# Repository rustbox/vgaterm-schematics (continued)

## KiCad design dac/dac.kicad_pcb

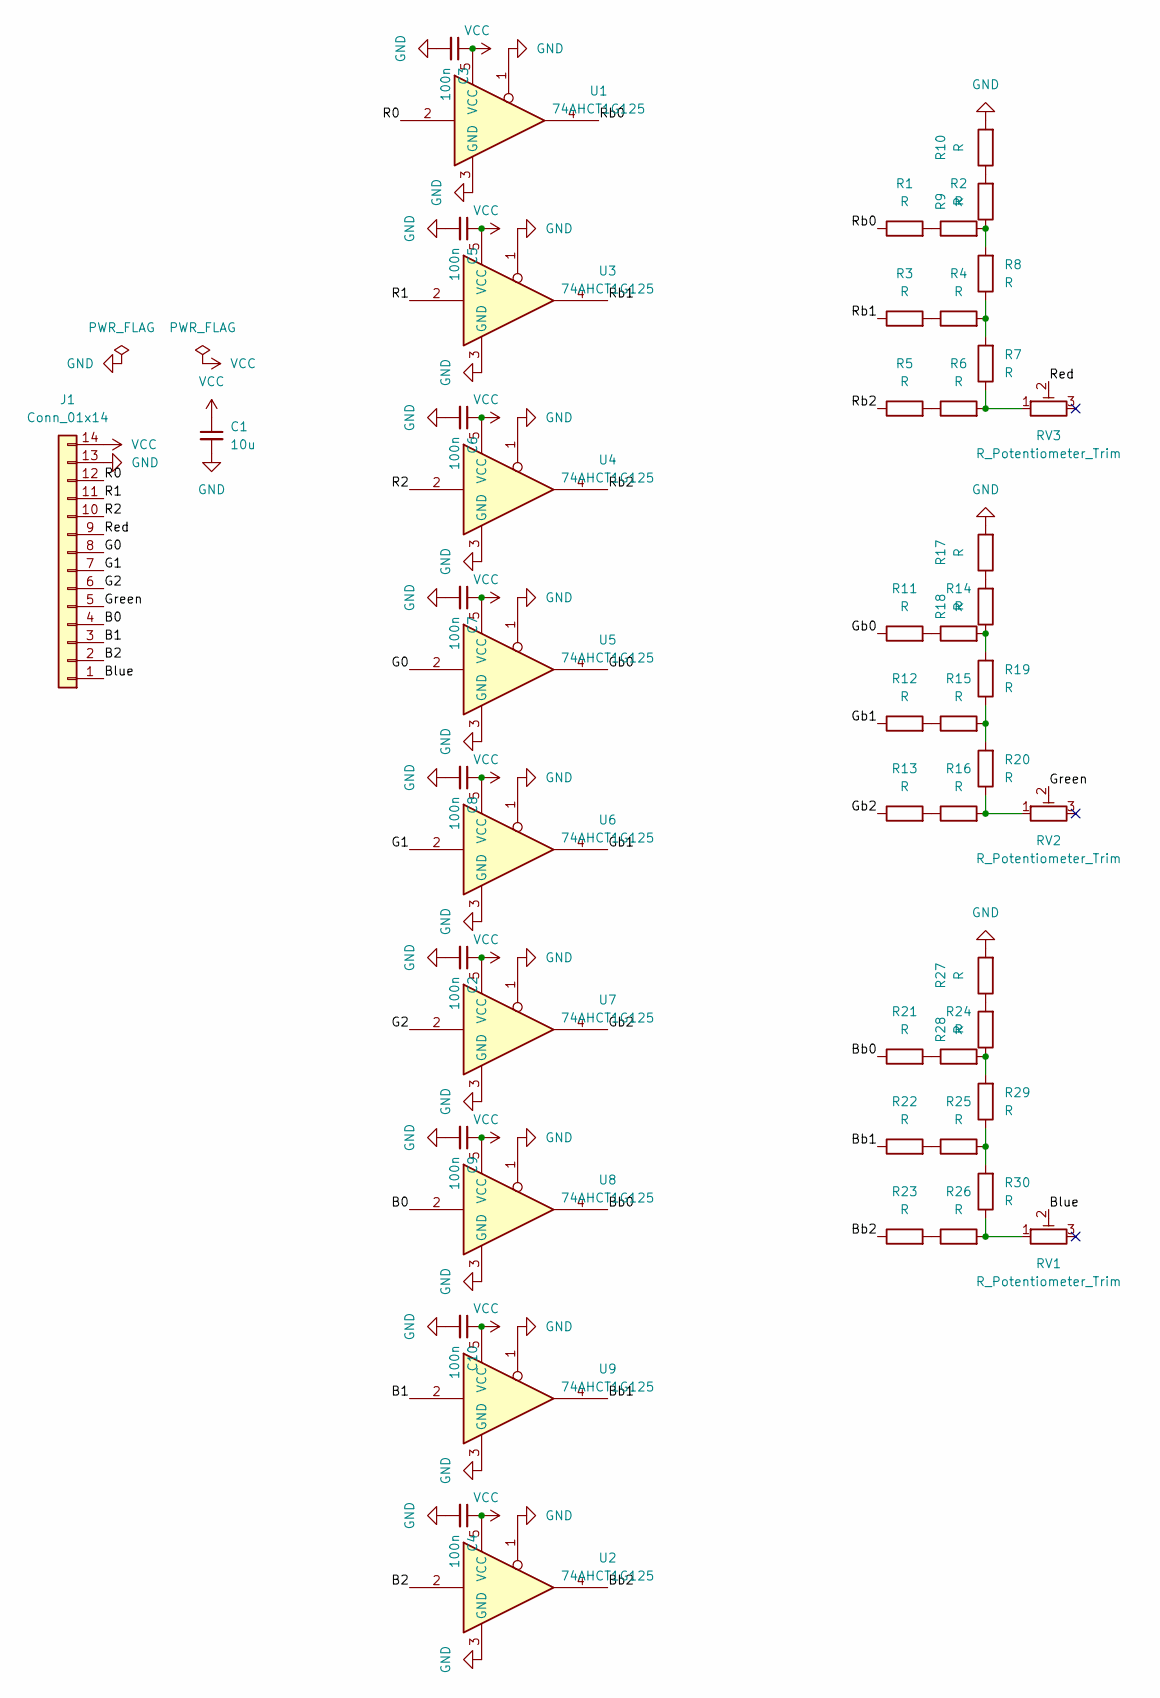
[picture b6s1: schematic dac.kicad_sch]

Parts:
C1: 10u; C_0805_2012Metric_Pad1.18x1.45mm_HandSolder
C2, C3, C4, C5, C6, C7, C8, C9, C10: 100n; C_0805_2012Metric_Pad1.18x1.45mm_HandSolder
J1: Conn_01x14; Harwin_M20-89014xx_1x14_P2.54mm_Horizontal
R1, R2, R3, R4, R5, R6, R7, R8, R9, R10, R11, R12, R13, R14, R15, R16, R17, R18, R19, R20, R21, R22, R23, R24, R25, R26, R27, R28, R29, R30: R; C_0805_2012Metric_Pad1.18x1.45mm_HandSolder
RV1, RV2, RV3: R_Potentiometer_Trim; TC33X2304E
U1, U2, U3, U4, U5, U6, U7, U8, U9: 74AHCT1G125; SOT-353_SC-70-5_Handsoldering

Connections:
/B0: J1.4, U8.2
/B1: J1.3, U9.2
/B2: J1.2, U2.2
/Bb0: R21.1, U8.4
/Bb1: R22.1, U9.4
/Bb2: R23.1, U2.4
/Blue: J1.1, RV1.2
/G0: J1.8, U5.2
/G1: J1.7, U6.2
/G2: J1.6, U7.2
/Gb0: R11.1, U5.4
/Gb1: R12.1, U6.4
/Gb2: R13.1, U7.4
/Green: J1.5, RV2.2
/R0: J1.12, U1.2
/R1: J1.11, U3.2
/R2: J1.10, U4.2
/Rb0: R1.1, U1.4
/Rb1: R3.1, U3.4
/Rb2: R5.1, U4.4
/Red: J1.9, RV3.2
GND: C1.2, C2.2, C3.2, C4.2, C5.2, C6.2, C7.2, C8.2, C9.2, C10.2, J1.13, R10.2, R17.2, R27.2, U1.1, U1.3 (GND), U2.1, U2.3 (GND), U3.1, U3.3 (GND), U4.1, U4.3 (GND), U5.1, U5.3 (GND), U6.1, U6.3 (GND), U7.1, U7.3 (GND), U8.1, U8.3 (GND), U9.1, U9.3 (GND)
unnamed: R1.2, R2.1
unnamed: R2.2, R8.2, R9.1
unnamed: R3.2, R4.1
unnamed: R4.2, R7.2, R8.1
unnamed: R5.2, R6.1
unnamed: R6.2, R7.1, RV3.1
unnamed: R9.2, R10.1
unnamed: R11.2, R14.1
unnamed: R12.2, R15.1
unnamed: R13.2, R16.1
unnamed: R14.2, R18.1, R19.2
unnamed: R15.2, R19.1, R20.2
unnamed: R16.2, R20.1, RV2.1
unnamed: R17.1, R18.2
unnamed: R21.2, R24.1
unnamed: R22.2, R25.1
unnamed: R23.2, R26.1
unnamed: R24.2, R28.1, R29.2
unnamed: R25.2, R29.1, R30.2
unnamed: R26.2, R30.1, RV1.1
unnamed: R27.1, R28.2
VCC: C1.1, C2.1, C3.1, C4.1, C5.1, C6.1, C7.1, C8.1, C9.1, C10.1, J1.14, U1.5 (VCC), U2.5 (VCC), U3.5 (VCC), U4.5 (VCC), U5.5 (VCC), U6.5 (VCC), U7.5 (VCC), U8.5 (VCC), U9.5 (VCC)

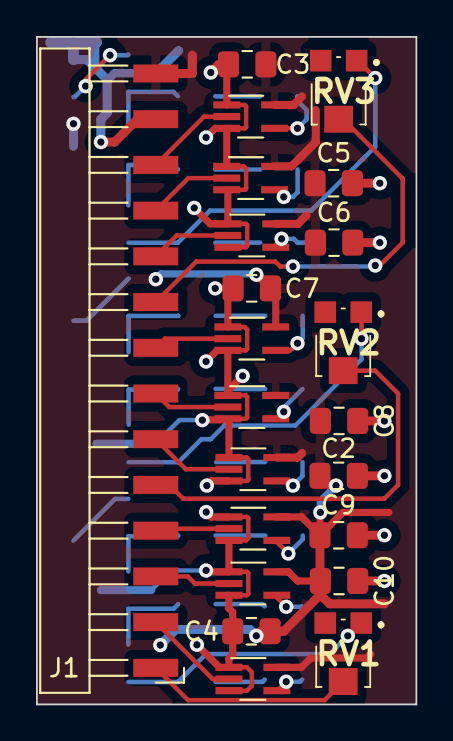
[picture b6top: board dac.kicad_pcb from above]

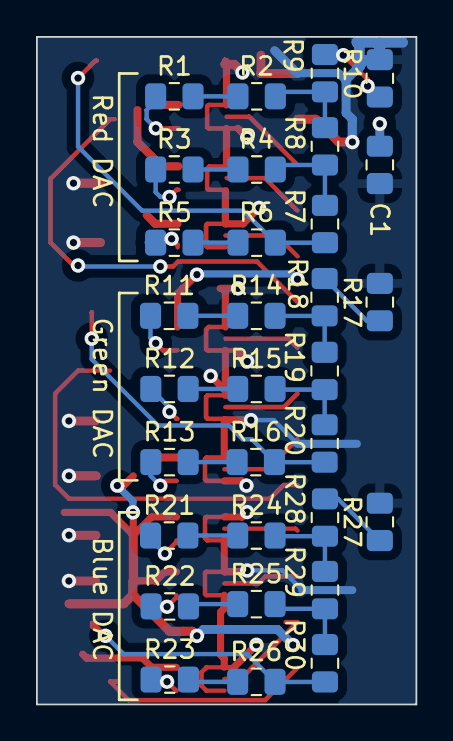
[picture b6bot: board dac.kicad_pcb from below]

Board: 2 copper layers, 21.1 x 37.1 mm, 53 parts (31 on the bottom side), 44 nets.

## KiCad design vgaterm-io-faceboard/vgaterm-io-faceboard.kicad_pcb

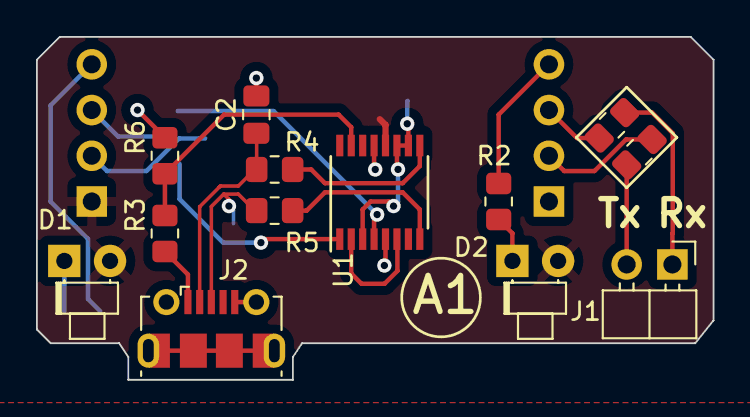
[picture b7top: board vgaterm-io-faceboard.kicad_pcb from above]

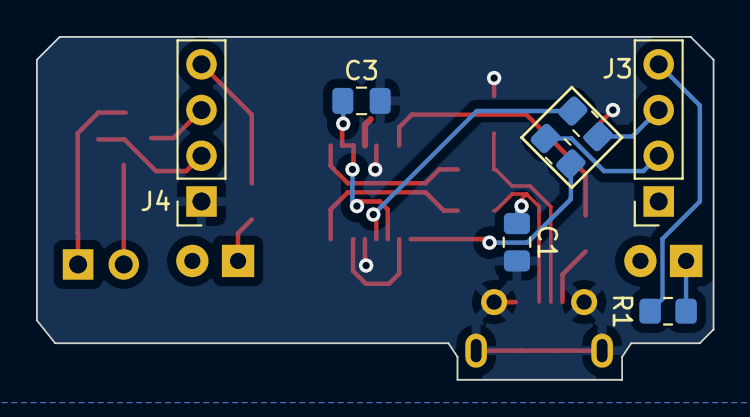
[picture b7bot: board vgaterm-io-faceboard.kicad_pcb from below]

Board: 2 copper layers, 37.6 x 19.1 mm, 20 parts (7 on the bottom side), 22 nets.

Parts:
C1, C2, C3: C_Small; C_0805_2012Metric_Pad1.18x1.45mm_HandSolder
D1, D2: LED; LED_D1.8mm_W1.8mm_H2.4mm_Horizontal_O1.27mm_Z1.6mm
J1: Conn_01x02; PinHeader_1x02_P2.54mm_Horizontal
J2: USB_B_Micro UART; USB_Micro-B_Molex-105017-0001
J3, J4: Conn_01x04; PinSocket_1x04_P2.54mm_Vertical
R1, R2: 1k; R_0805_2012Metric_Pad1.20x1.40mm_HandSolder
R3: 4.7k; R_0805_2012Metric_Pad1.20x1.40mm_HandSolder
R4, R5: 27; R_0805_2012Metric_Pad1.20x1.40mm_HandSolder
R6: 10k; R_0805_2012Metric_Pad1.20x1.40mm_HandSolder
R7, R8, R9, R10: R; R_0805_2012Metric_Pad1.20x1.40mm_HandSolder
U1: FT230XS; SSOP-16_3.9x4.9mm_P0.635mm

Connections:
/3v3: C3.1, U1.3 (VCCIO), U1.10 (3V3OUT), U1.11 (~RESET)
/D+: C1.1, J2.3 (D+), R5.1
/D-: C2.1, J2.2 (D-), R4.1
/RXI_{0}: R8.2, U1.4 (RXD)
/RXI_{1}: J1.1, R10.2
/S_{0}: J3.4, R1.2
/S_{1}: J4.4, R2.2
/TXI_{0}: R7.1, U1.1 (TXD)
/TXI_{1}: J1.2, R9.1
/V_sense: R3.2, R6.1, U1.15 (CBUS0)
GND: C1.2, C2.2, C3.2, J2.5 (GND), J2.6 (Shield), J4.1, R6.2, U1.5 (GND), U1.13 (GND)
unnamed: D1.1 (K), R1.1
unnamed: D2.1 (K), R2.1
unnamed: J2.1 (VBUS), R3.1
unnamed: J3.2, R7.2
unnamed: J3.3, R8.1
unnamed: J4.2, R9.2
unnamed: J4.3, R10.1
unnamed: R4.2, U1.9 (USBDM)
unnamed: R5.2, U1.8 (USBDP)
unnamed: U1.2 (~RTS), U1.6 (~CTS)
VCC: D1.2 (A), D2.2 (A), J3.1, U1.12 (VCC)

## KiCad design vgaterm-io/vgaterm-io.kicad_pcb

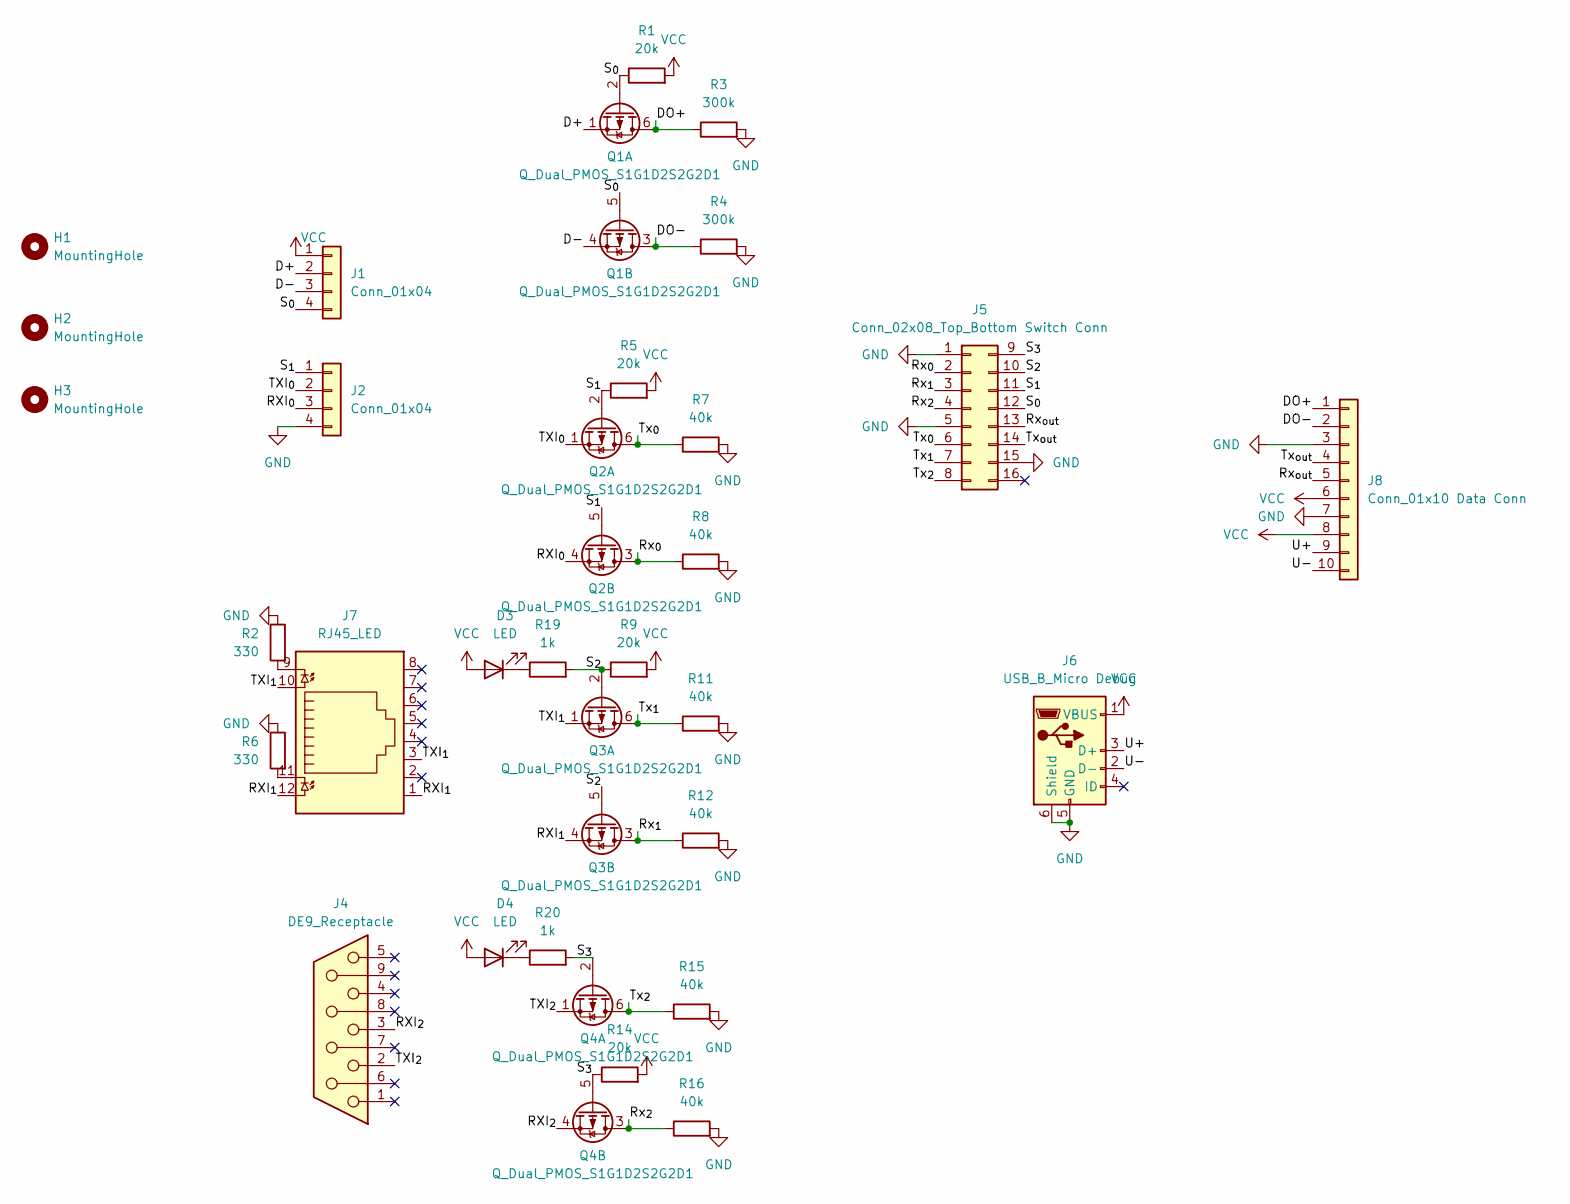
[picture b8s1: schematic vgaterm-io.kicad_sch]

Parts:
D3, D4: LED; LED_D1.8mm_W1.8mm_H2.4mm_Horizontal_O1.27mm_Z1.6mm
H1, H2, H3: MountingHole; MountingHole_2.2mm_M2_ISO7380
J1, J2: Conn_01x04; PinHeader_1x04_P2.54mm_Vertical
J4: DE9_Receptacle; DSUB-9_Female_Horizontal_P2.77x2.84mm_EdgePinOffset4.94mm_H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
J5: Conn_02x08_Top_Bottom Switch Conn; PinHeader_2x08_P2.54mm_Horizontal
J6: USB_B_Micro Debug; USB_Micro-B_Molex-105017-0001
J7: RJ45_LED; RJ45_Amphenol_RJHSE538X
J8: Conn_01x10 Data Conn; PinHeader_2x05_P2.54mm_Horizontal
Q1, Q2, Q3, Q4: Q_Dual_PMOS_S1G1D2S2G2D1; SOT-363_SC-70-6_Handsoldering
R1, R5, R9, R14: 20k; R_0805_2012Metric_Pad1.20x1.40mm_HandSolder
R2, R6: 330; R_0805_2012Metric_Pad1.20x1.40mm_HandSolder
R3, R4: 300k; R_0805_2012Metric_Pad1.20x1.40mm_HandSolder
R7, R8, R11, R12, R15, R16: 40k; R_0805_2012Metric_Pad1.20x1.40mm_HandSolder
R19, R20: 1k; R_0805_2012Metric_Pad1.20x1.40mm_HandSolder

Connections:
/D+: J1.2, Q1.1 (S)
/D-: J1.3, Q1.4 (S)
/DO+: J8.1, Q1.6 (D), R3.1
/DO-: J8.2, Q1.3 (D), R4.1
/RXI_{0}: J2.3, Q2.4 (S)
/RXI_{1}: J7.1, J7.12, Q3.4 (S)
/RXI_{2}: J4.3, Q4.4 (S)
/Rx_{0}: J5.2, Q2.3 (D), R8.1
/Rx_{1}: J5.3, Q3.3 (D), R12.1
/Rx_{2}: J5.4, Q4.3 (D), R16.1
/Rx_{out}: J5.13, J8.5
/S_{0}: J1.4, J5.12, Q1.2 (G), Q1.5 (G), R1.1
/S_{1}: J2.1, J5.11, Q2.2 (G), Q2.5 (G), R5.1
/S_{2}: J5.10, Q3.2 (G), Q3.5 (G), R9.1, R19.2
/S_{3}: J5.9, Q4.2 (G), Q4.5 (G), R14.1, R20.2
/TXI_{0}: J2.2, Q2.1 (S)
/TXI_{1}: J7.3, J7.10, Q3.1 (S)
/TXI_{2}: J4.2, Q4.1 (S)
/Tx_{0}: J5.6, Q2.6 (D), R7.1
/Tx_{1}: J5.7, Q3.6 (D), R11.1
/Tx_{2}: J5.8, Q4.6 (D), R15.1
/Tx_{out}: J5.14, J8.4
/U+: J6.3 (D+), J8.9
/U-: J6.2 (D-), J8.10
GND: J2.4, J5.1, J5.5, J5.15, J6.5 (GND), J6.6 (Shield), J8.3, J8.7, R2.1, R3.2, R4.2, R6.1, R7.2, R8.2, R11.2, R12.2, R15.2, R16.2
unnamed: D3.1 (K), R19.1
unnamed: D4.1 (K), R20.1
unnamed: J7.9, R2.2
unnamed: J7.11, R6.2
VCC: D3.2 (A), D4.2 (A), J1.1, J6.1 (VBUS), J8.6, J8.8, R1.2, R5.2, R9.2, R14.2

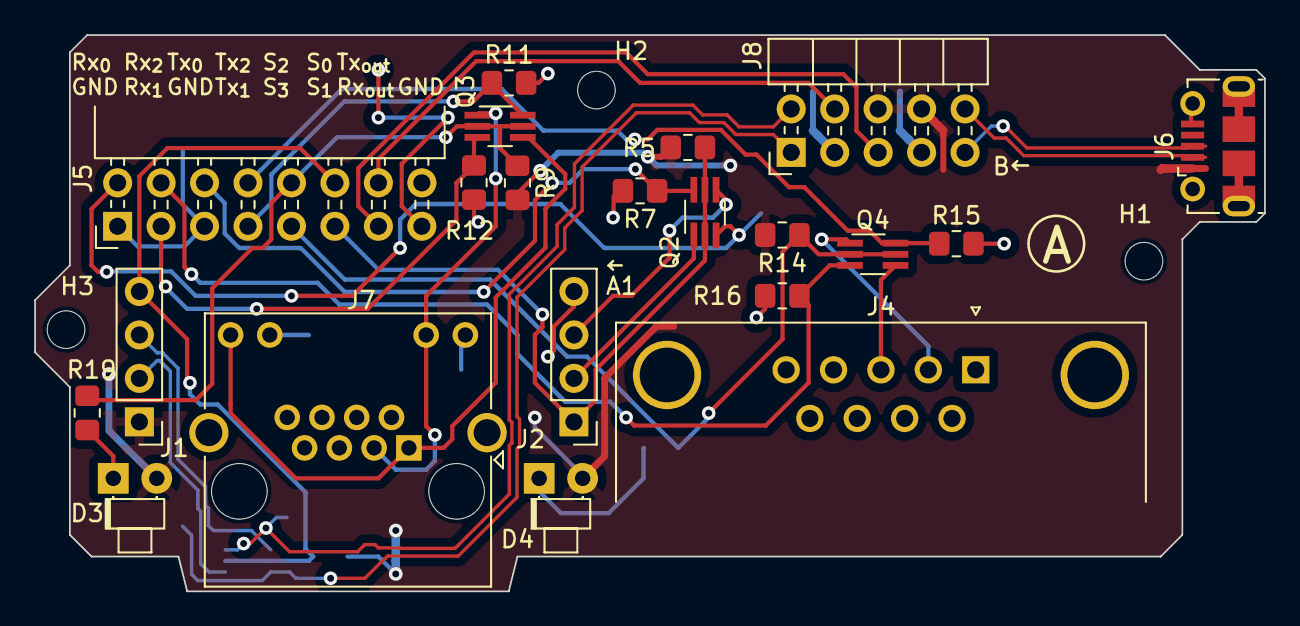
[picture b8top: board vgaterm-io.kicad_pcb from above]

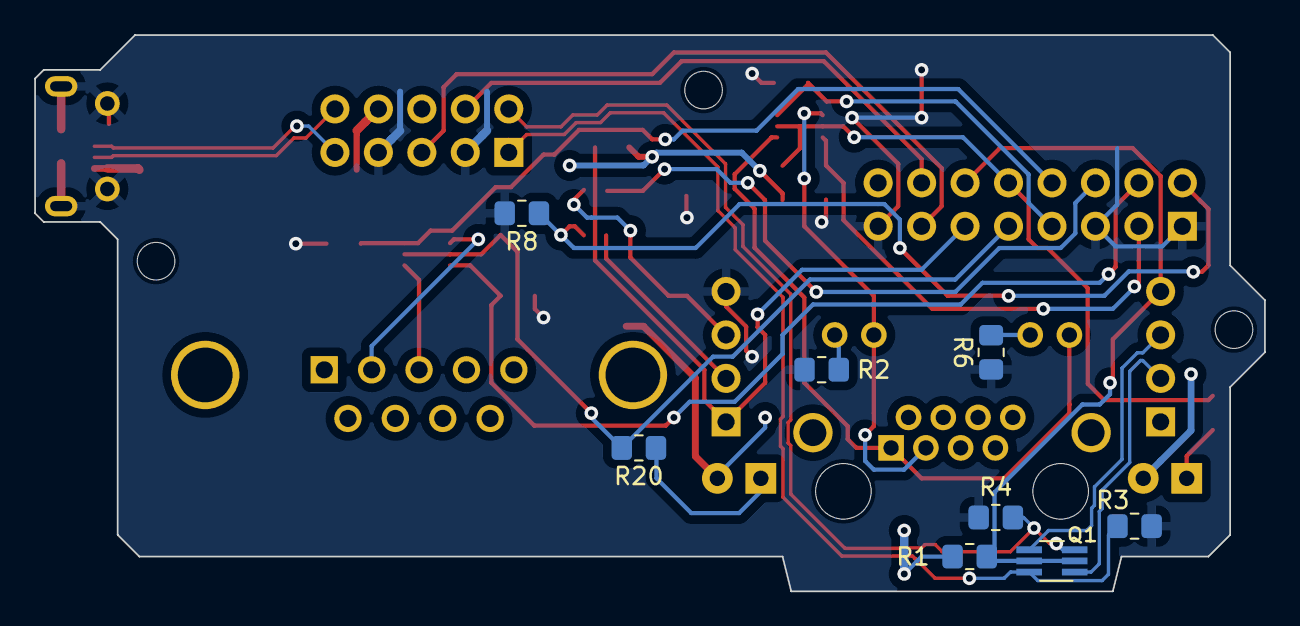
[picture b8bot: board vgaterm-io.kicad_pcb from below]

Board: 2 copper layers, 71.9 x 32.5 mm, 32 parts (8 on the bottom side), 30 nets.

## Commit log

2023-10-14 initial commit of vgaterm schematics designed for to be placed in an enclosure
2023-10-18 updating board based on convos with Seth
2023-10-18 adding an led board that can connect to vgaterm
2023-10-18 updating timing board hsync vsync delay
2023-10-25 board updates and adding vga breakout
2023-10-28 maybe a separte dac board
2023-11-01 timing board updates and adding keyboard loft board and vga breakout
2023-11-02 timing board routed and labeled with no errors
2024-02-27 current boards
2024-02-29 small updates
2024-03-06 initial rework for all smd on one side and all IO on bottom board
